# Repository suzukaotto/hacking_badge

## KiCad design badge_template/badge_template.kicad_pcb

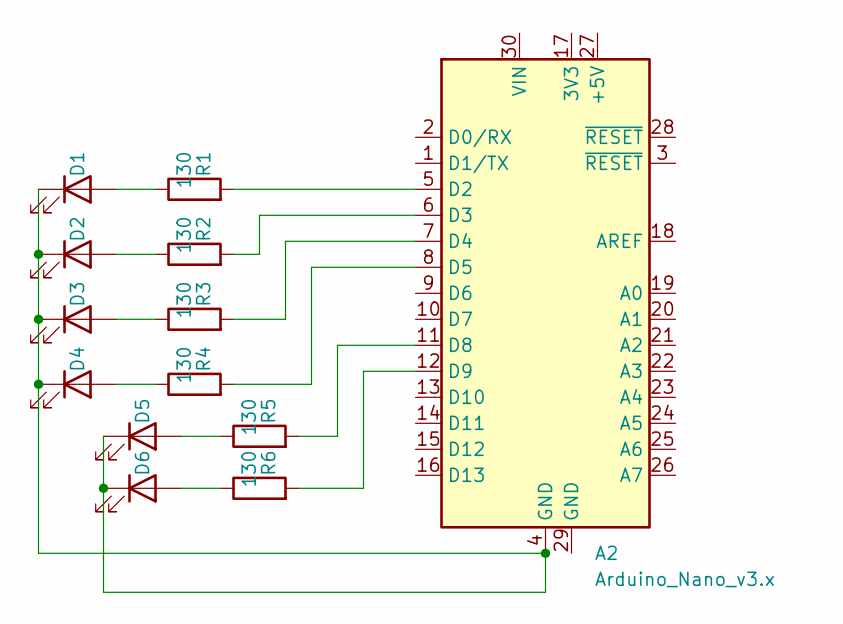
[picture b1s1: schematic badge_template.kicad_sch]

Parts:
A2: Arduino_Nano_v3.x; Arduino_Nano
D1, D2, D3, D4, D5, D6: LED; LED_0603_1608Metric
R1, R2, R3, R4, R5, R6: 130; LED_0201_0603Metric

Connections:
unnamed: A2.5 (D2), R1.2
unnamed: A2.6 (D3), R2.2
unnamed: A2.7 (D4), R3.2
unnamed: A2.8 (D5), R4.2
unnamed: A2.11 (D8), R5.2
unnamed: A2.12 (D9), R6.2
unnamed: D1.2 (A), R1.1
unnamed: A2.4 (GND), D1.1 (K), D2.1 (K), D3.1 (K), D4.1 (K), D5.1 (K), D6.1 (K)
unnamed: D2.2 (A), R2.1
unnamed: D3.2 (A), R3.1
unnamed: D4.2 (A), R4.1
unnamed: D5.2 (A), R5.1
unnamed: D6.2 (A), R6.1

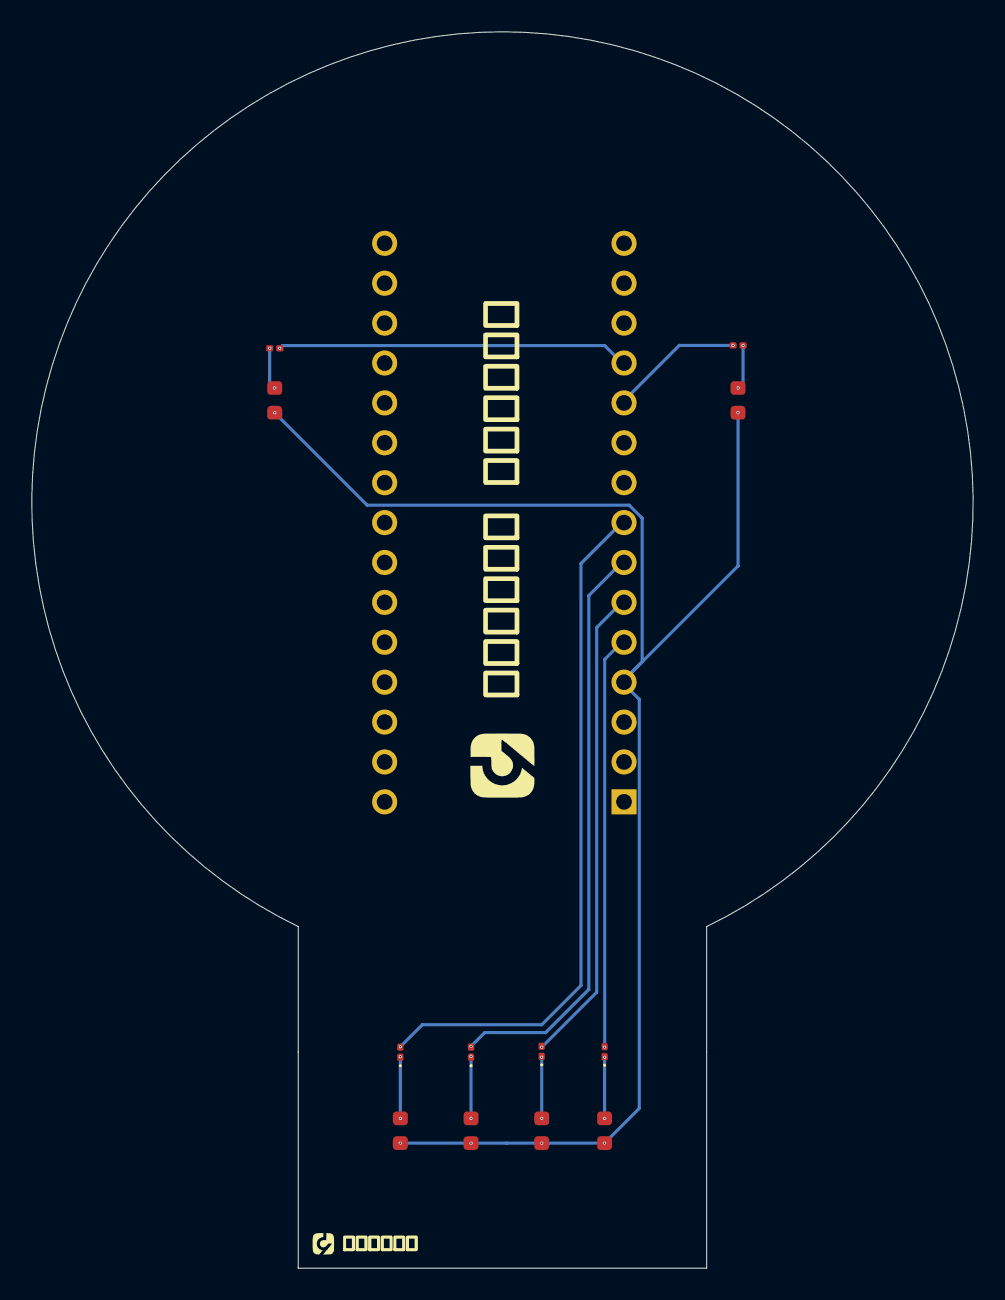
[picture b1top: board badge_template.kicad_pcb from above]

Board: 2 copper layers, 59.9 x 78.7 mm, 13 parts (0 on the bottom side), 13 nets.

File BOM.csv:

Reference,Value,Datasheet,Footprint,Qty,DNP
A1,Arduino_Nano_v2.x,https://www.arduino.cc/en/uploads/Main/ArduinoNanoManual23.pdf,Module:Arduino_Nano,1,
"D1,D2,D3,D4,D5,D6",LED,~,LED_SMD:LED_0603_1608Metric,6,
"R1,R2,R3,R4,R5,R6",130,~,LED_SMD:LED_0201_0603Metric,6,

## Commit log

2024-11-15 update: repo create
2024-11-17 update: pcb update
